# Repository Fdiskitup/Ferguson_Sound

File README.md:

# Ferguson_Sound
A soundcard for the Ferguson Big Board based on the SN76489 PSG sound chip.   

The parallel port on the Ferguson Big Board uses the Z80 PIO to give 2 x 8bit bidirectional user ports.  
This soundcard was created to make use of port A. 

The board itself is rather simple consisting of 3 parts. 

1, The programmable sound generator chip (PSG) SN76489 and clock crystal oscillator. 
2, The amplifier based on he classic LM386 op amp chip. 
3, The VU meter using LM3915N-1 to pulse the LED's in tune to the music.  

This is derived from several sources 
https://github.com/bchiha/Ready-Z80/tree/main/16-SN76489_Sound_Generator 

https://github.com/jblang/SN76489

https://github.com/abaffa/z80cpm_emulator

What Does it do ? 
well it can output 3 channels of tones simultaneously, like a cord.  plus it can output a 4th noise channel for explosions gunshots etc. 
you can program it from basic, assembly, pascal, C etc.  
remember you will need to set up the PIO Port to be unidirectional - i.e. data mode as output, before trying to send data to the PSG.  
Included here are some basic files to get you started making noises.  
More importantly there is a program here M.COM that will mute the sound chip, because when it first turns on it tends to emit a random tone.  You'll want to stop this.

perhaps more interesting is the ability to play VGM files - these are Video Game Music files. 
The disk images here contain several files "filename.vgm" to play a vgm file simply type : 
VGMPLAY filename.VGM  [then Return/Enter]

to deal with the issue of speed I have recomplied the VGMPLAY.COM with different delays, 4VGMPLAY.COM is fastest while 7VGMPLAY.COM is slowest.
Speed mismatches occur because the PSG clock crystal (4MHZ) used may not be the same as that in the origin system.   

The 270nF capacitors on the BOM are a strange value but it will be fine with 220nF or 300nF.  Hobby engineering. 

So you've built the card: 

On the Big Board make sure you set the jumpers pins 7-8, 9-10, 11-12, 13-14, 15-16 all on.  This sets the port for output only from the hardware.
see the single blue jumper and the 4 red jumpers.  

You'll need to give the board +5V, I just brought a cable from the main board power block to the soundcard power block.  
The ground plane is connected to the 10 ground pins of the connector so you could just wire in a single 5V from the rails directly below the power connector.

JP1 = selects non-amplified or amplified output.  Non amplified goes to the 3.5 mm Jack then into powered speakers.   Amplified out can go direct into a 8ohm speaker or if to connect an RCA jack direct into a TV.   
JP2 = selects bar or dot mode for the VU meter (if installed) 
JP3 = selects to use internal audio for the VU meter, or external input for the VU meter (really just to test it.).    

I have tried with the 4MHZ full size dip 16 crystal oscillator, but I put in the footprint for the smaller oscillator package.  it should accomodate other frequencies 3.57mhz etc.  or you can steal a clock signal from the Z80-PIO pin 25 (Bandit !). 
similarly you can just jumper the power switch so its always on - you can always turn it down with the pot.       

So once it is built and jumpered, switch on and you should be treated to some excellent feedback.  
quickly boot into CPM and run the M.COM file to mute the noise, phew. 

The port resides at 08 and 09 hex

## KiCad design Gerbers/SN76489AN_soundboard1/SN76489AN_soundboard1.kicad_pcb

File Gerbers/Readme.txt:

These Gerbers were used to make a set of boards with PCBWAY in April of 2025.  The Board was built and tested.  
comments : 
1, The 0.27uF (270nF) caps were substituted with 0.22uF (220nF) ceramics and the amp circuit works fine.
2, The slide switch on the power line stops the random feedback at power on, I did not have the exact switch so used a substitute.  The M.com file mutes the PSG on boot and if needed with a hanging note etc. 
3, The VU meter bottom 2 LED's stay on at all times and the sensitivity of the VU meter is attenuated too much by the volume POT.  Resistor and/or cap values need fine tuning.

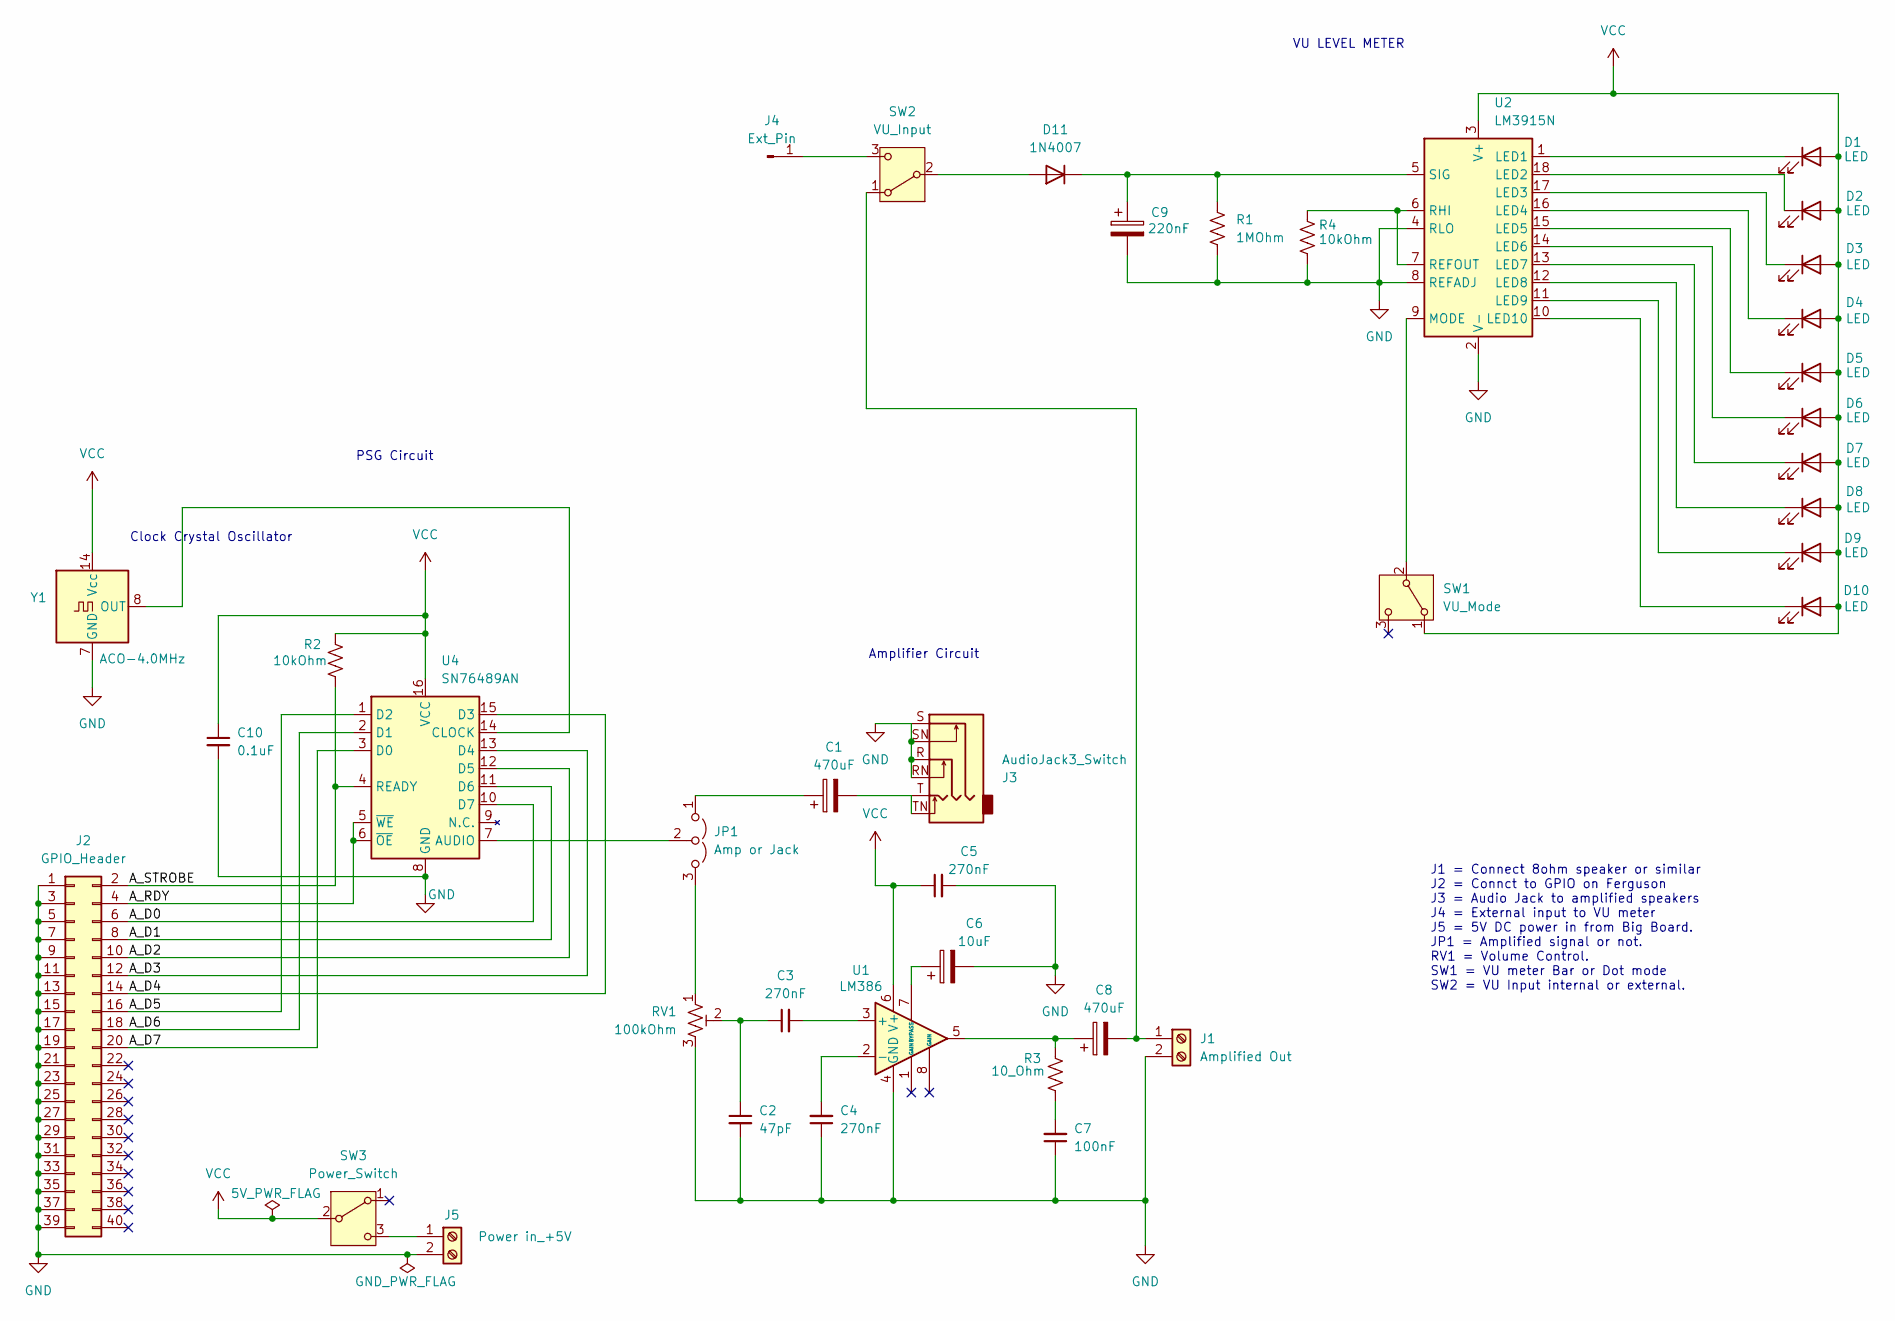
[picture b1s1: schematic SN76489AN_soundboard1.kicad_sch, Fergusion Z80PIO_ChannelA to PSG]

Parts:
C1: 470uF; CP_Radial_D10.0mm_P2.50mm
C2: 47pF; CP_Radial_D5.0mm_P2.50mm
C3, C4, C5: 270nF; CP_Radial_D5.0mm_P2.50mm
C6: 10uF; CP_Radial_D5.0mm_P2.50mm
C7: 100nF; CP_Radial_D5.0mm_P2.50mm
C8: 470uF; C_Radial_D10.0mm_H12.5mm_P5.00mm
C9: 220nF; CP_Radial_D5.0mm_P2.50mm
C10: 0.1uF; CP_Radial_D5.0mm_P2.50mm
D1, D2, D3, D4, D5, D6, D7, D8, D9, D10: LED; LED_D3.0mm
D11: 1N4007; D_DO-41_SOD81_P10.16mm_Horizontal
J1: Amplified Out; TerminalBlock_MaiXu_MX126-5.0-02P_1x02_P5.00mm
J2: GPIO_Header; PinSocket_2x20_P2.54mm_Vertical
J3: AudioJack3_Switch; Jack_3.5mm_PJ31060-I_Horizontal
J4: Ext_Pin; PinHeader_1x01_P2.54mm_Horizontal
J5: Power in_+5V; TerminalBlock_MaiXu_MX126-5.0-02P_1x02_P5.00mm
JP1: Amp or Jack; PinHeader_1x03_P2.54mm_Vertical
R1: 1MOhm; R_Axial_DIN0207_L6.3mm_D2.5mm_P10.16mm_Horizontal
R2, R4: 10kOhm; R_Axial_DIN0207_L6.3mm_D2.5mm_P10.16mm_Horizontal
R3: 10_Ohm; R_Axial_DIN0207_L6.3mm_D2.5mm_P10.16mm_Horizontal
RV1: 100kOhm; Potentiometer_Bourns_PTV09A-1_Single_Vertical
SW1: VU_Mode; PinHeader_1x03_P2.54mm_Vertical
SW2: VU_Input; PinHeader_1x03_P2.54mm_Vertical
SW3: Power_Switch; SW_E-Switch_EG1224_SPDT_Angled
U1: LM386; DIP-8-16_W7.62mm_Socket_LongPads
U2: LM3915N; DIP-18_W7.62mm
U4: SN76489AN; DIP-16_W7.62mm
Y1: ACO-4.0MHz; Oscillator_DIP-14

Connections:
/A_D0: J2.6, U4.10 (D7)
/A_D1: J2.8, U4.11 (D6)
/A_D2: J2.10, U4.12 (D5)
/A_D3: J2.12, U4.13 (D4)
/A_D4: J2.14, U4.15 (D3)
/A_D5: J2.16, U4.1 (D2)
/A_D6: J2.18, U4.2 (D1)
/A_D7: J2.20, U4.3 (D0)
/A_RDY: J2.4, U4.5 (~WE), U4.6 (~OE)
/A_STROBE: J2.2, R2.2, U4.4 (READY)
GND: C2.2, C4.1, C5.2, C6.2, C7.1, C9.2, C10.2, J1.2, J2.1, J2.3, J2.5, J2.7, J2.9, J2.11, J2.13, J2.15, J2.17, J2.19, J2.21, J2.23, J2.25, J2.27, J2.29, J2.31, J2.33, J2.35, J2.37, J2.39, J3.R, J3.RN, J3.S, J3.SN, J5.2, R1.2, R4.2, RV1.3, U1.4 (GND), U2.2 (V-), U2.4 (RLO), U2.8 (REFADJ), U4.8 (GND), Y1.7 (GND); also elsewhere on the board
unnamed: C1.2, J3.T, J3.TN
unnamed: C2.1, C3.1, RV1.2
unnamed: C7.2, R3.2
unnamed: C8.1, R3.1, U1.5
unnamed: D1.1 (K), U2.1 (LED1)
unnamed: D2.1 (K), U2.18 (LED2)
unnamed: D3.1 (K), U2.17 (LED3)
unnamed: D4.1 (K), U2.16 (LED4)
unnamed: D5.1 (K), U2.15 (LED5)
unnamed: D6.1 (K), U2.14 (LED6)
unnamed: D7.1 (K), U2.13 (LED7)
unnamed: D8.1 (K), U2.12 (LED8)
unnamed: D9.1 (K), U2.11 (LED9)
unnamed: D10.1 (K), U2.10 (LED10)
unnamed 25: D11.2 (A), SW2.2 (B); also elsewhere on the board
unnamed: C9.1, D11.1 (K), R1.1, U2.5 (SIG)
unnamed 27: C8.2, J1.1, SW2.1 (A); also elsewhere on the board
unnamed 28: J4.1, SW2.3 (C); also elsewhere on the board
unnamed: J5.1, SW3.3 (C)
unnamed: C1.1, JP1.1 (A)
unnamed: JP1.3 (B), RV1.1
unnamed: JP1.2 (C), U4.7 (AUDIO)
unnamed 33: SW1.2 (B), U2.9 (MODE); also elsewhere on the board
unnamed: C3.2, U1.3 (+)
unnamed: C4.2, U1.2 (-)
unnamed: C6.1, U1.7 (BYPASS)
unnamed: R4.1, U2.6 (RHI), U2.7 (REFOUT)
unnamed 38: U4.14 (CLOCK), Y1.8 (OUT); also elsewhere on the board
VCC: C5.1, C10.1, D1.2 (A), D2.2 (A), D3.2 (A), D4.2 (A), D5.2 (A), D6.2 (A), D7.2 (A), D8.2 (A), D9.2 (A), D10.2 (A), R2.1, SW1.1 (A), SW3.2 (B), U1.6 (V+), U2.3 (V+), U4.16 (VCC), Y1.14 (Vcc); also elsewhere on the board

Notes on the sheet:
PSG Circuit
J1 = Connect 8ohm speaker or similar J2 = Connct to GPIO on Ferguson J3 = Audio Jack to amplified speakers J4 = External input to VU meter J5 = 5V DC power in from Big Board. JP1 = Amplified signal or not. RV1 = Volume Control. SW1 = VU meter Bar or Dot mode SW2 = VU Input internal or external.
Clock Crystal Oscillator
Amplifier Circuit
VU LEVEL METER

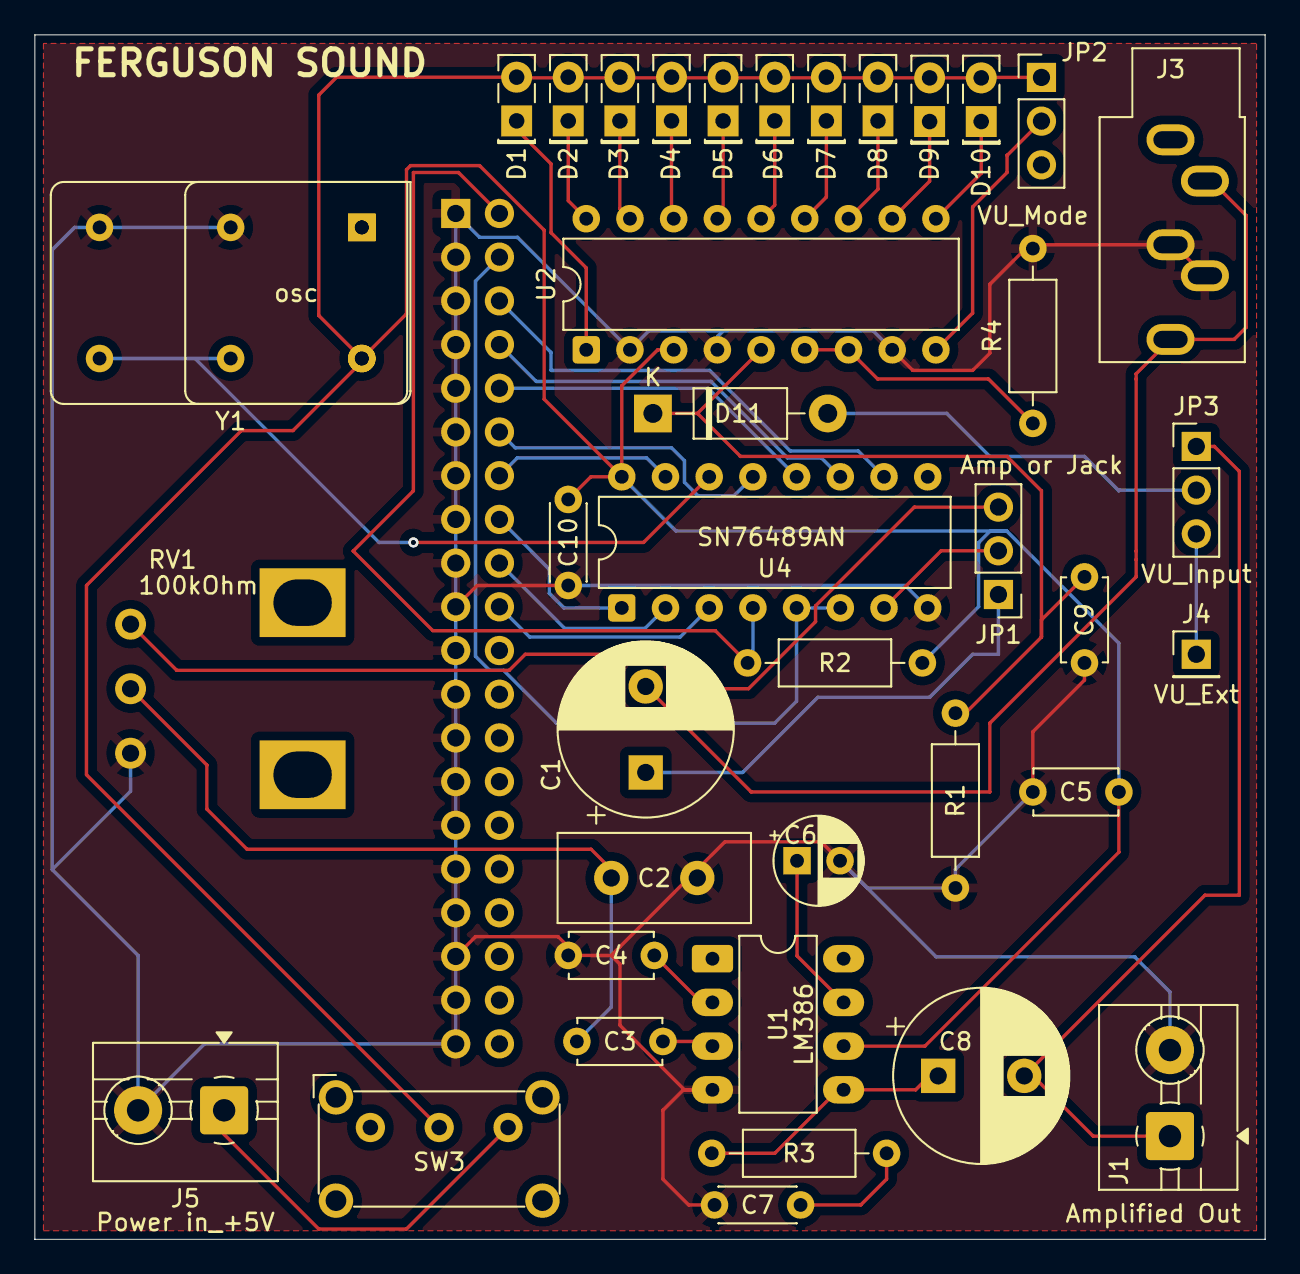
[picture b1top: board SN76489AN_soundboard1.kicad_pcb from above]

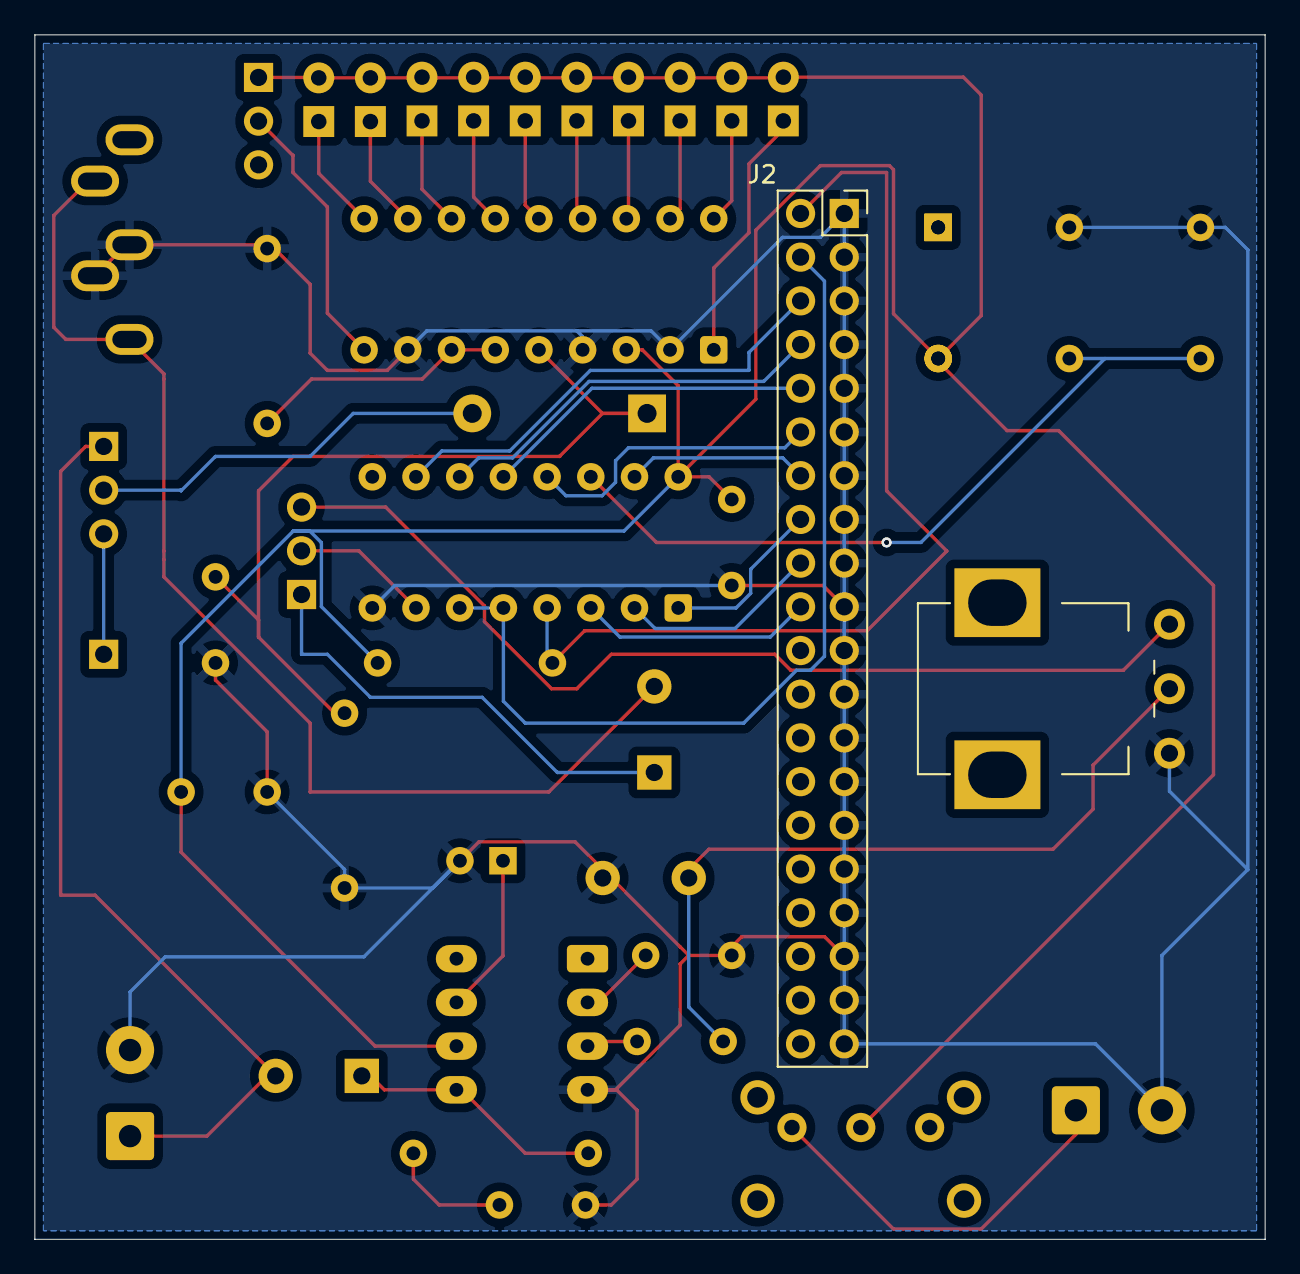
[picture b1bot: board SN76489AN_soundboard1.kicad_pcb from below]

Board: 2 copper layers, 71.5 x 70.0 mm, 40 parts (2 on the bottom side), 40 nets.

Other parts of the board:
JP2: VU_Mode; PinHeader_1x03_P2.54mm_Vertical
JP3: VU_Input; PinHeader_1x03_P2.54mm_Vertical
osc: Oscillator_DIP-8

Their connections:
GND: osc.4; also elsewhere on the board
unnamed 25: JP3.2 (B); also elsewhere on the board
unnamed 27: JP3.1 (A); also elsewhere on the board
unnamed 28: JP3.3 (C); also elsewhere on the board
unnamed 33: JP2.2 (B); also elsewhere on the board
unnamed 38: osc.5; also elsewhere on the board
VCC: JP2.1 (A), osc.8; also elsewhere on the board

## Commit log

2025-04-19 Update README.md
    first edit
2025-04-19 Add files via upload
    VGMPLAYER for CPM on the Fergusson Big Board. Compiled COM file is for the 4MHz Big Board and the Ferguson Sound card with a 4MHz crystal.
2025-04-19 Create Readme.txt
    descriptive text
2025-04-19 Add files via upload
    ferguson_sound.zip is the file you need to upload to PCB manufacturing house JLPCB or PCBWAY
2025-04-19 Create LED_Alignment
2025-04-19 Create Volume_Knob
2025-04-19 Create notes.md
    Spelling!
2025-05-09 Add files via upload
    added part numbers for ordering from Digikey
